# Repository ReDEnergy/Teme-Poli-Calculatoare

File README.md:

Golden Box
===============

#### Teme, proiecte si laboratoare - Calculatoare 2010 - 2014 - Politehnica Bucuresti  

	Autor: Gabriel Ivanica

Aici gasiti cam toate proiectele si temele pe care le-am avut de facut in cei 4 ani de facultate  
**Toate sunt implementari personale, exceptie facand cateva proiecte de echipa**

## ATENTIE
+ Scopul acestui repo nu e sa ofere o sursa de copy/paste am trecut materia... ci o sursa de informare, idei si ajutor
+ Temele vin insotite de explicatii extrem de detaliate in **README** (100+ linii) + bonus ASCII ART

**Daca se intampla sa aveti fix aceasi tema, nu fiti fraieri sa credeti ca va merge cu copy-paste**
+ asistentii se prind de la o posta cand e vorba de copiat si adio punctaj pe teme
+ deci, 99% sanse sa repeti materia daca copiezi

## Statistici
+ tot ce am pus compileaza si ruleaza 100%
+ 95% sunt complete 100/100 (in teste sau VM Checker) + bonus (daca exista)
+ in cazul in care lipsesc cerintele se pot deduce usor din README
+ facut aproape toate temele (exceptie, cateva cazuri limita de complexitate sau lene)
+ pentru anumite materii gasiti si laboratoare

## Recomandari
+ Cititi README, va uitati peste surse, rulati si testati, dar implementarea sa fie personala
+ Temele din anii III si IV sunt cele mai interesante si complexe
+ la SGP gasiti chestii interesante, foarte bune pentru proiectele de grafica din anii III sau IV (un mic Engine Grafic, tehnici de randare: deferred rendering, screen space ambient occlusion, shadows, tesselation, si multe altele)

##### Daca aveti sugestii sau recomandari adaugati un *issue*

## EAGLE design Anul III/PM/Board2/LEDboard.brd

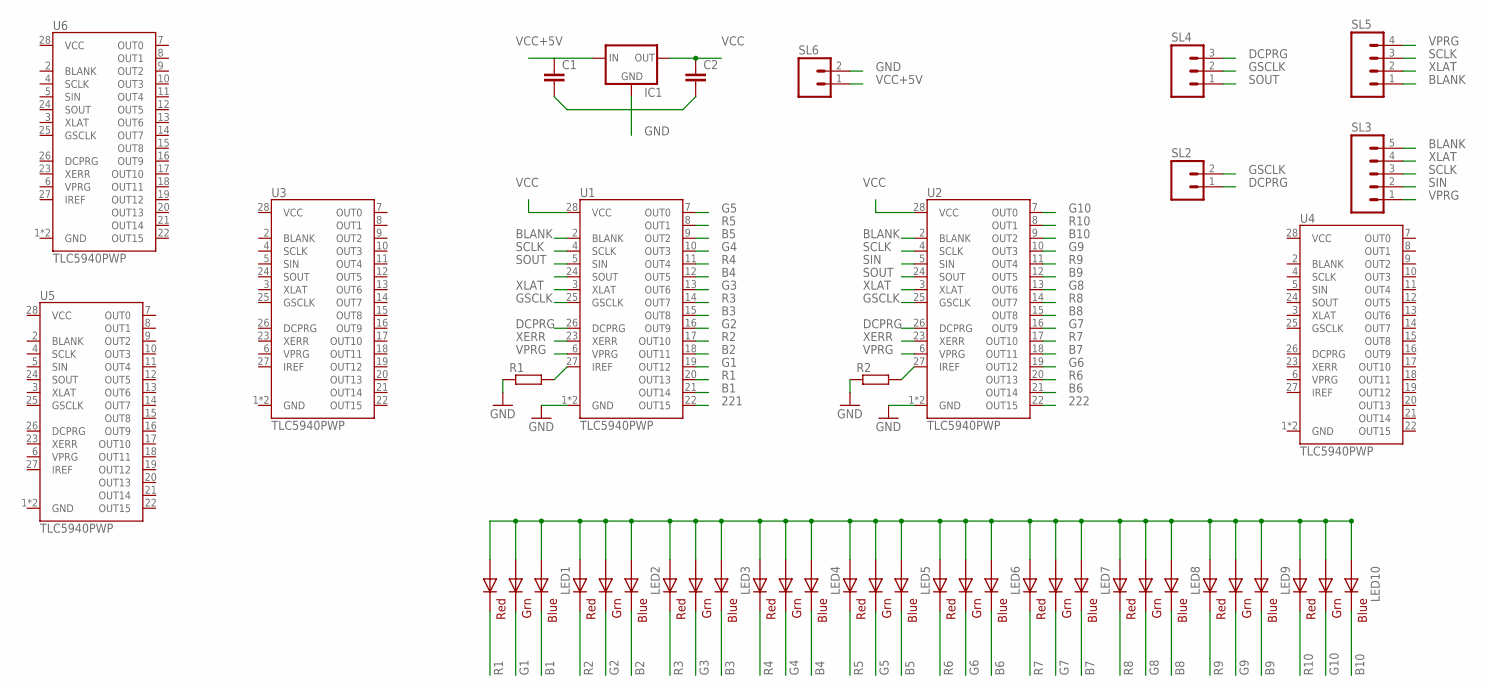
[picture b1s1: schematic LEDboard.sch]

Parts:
C1, C2: C-EU050-025X075; C050-025X075
IC1: 78XXL
LED1, LED2, LED3, LED4, LED5, LED6, LED7, LED8, LED9, LED10: RGBLED5050
R1, R2: R-EU_M1406; M1406
SL2, SL6: M02; 02P
SL3: M05; 05P
SL4: M03; 03P
SL5: M04; 04P
U1, U2, U3, U4, U5, U6: TLC5940PWP; TSSOP28-GROUNDPAD

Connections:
221: U1.22 (OUT15)
222: U2.22 (OUT15)
B1: LED1.4 (BLUE_C), U1.21 (OUT14)
B2: LED2.4 (BLUE_C), U1.18 (OUT11)
B3: LED3.4 (BLUE_C), U1.15 (OUT8)
B4: LED4.4 (BLUE_C), U1.12 (OUT5)
B5: LED5.4 (BLUE_C), U1.9 (OUT2)
B6: LED6.4 (BLUE_C), U2.21 (OUT14)
B7: LED7.4 (BLUE_C), U2.18 (OUT11)
B8: LED8.4 (BLUE_C), U2.15 (OUT8)
B9: LED9.4 (BLUE_C), U2.12 (OUT5)
B10: LED10.4 (BLUE_C), U2.9 (OUT2)
BLANK: SL3.5, SL5.1, U1.2 (BLANK), U2.2 (BLANK)
DCPRG: SL2.1, SL4.3, U1.26 (DCPRG), U2.26 (DCPRG)
G1: LED1.6 (GREEN_C), U1.19 (OUT12)
G2: LED2.6 (GREEN_C), U1.16 (OUT9)
G3: LED3.6 (GREEN_C), U1.13 (OUT6)
G4: LED4.6 (GREEN_C), U1.10 (OUT3)
G5: LED5.6 (GREEN_C), U1.7 (OUT0)
G6: LED6.6 (GREEN_C), U2.19 (OUT12)
G7: LED7.6 (GREEN_C), U2.16 (OUT9)
G8: LED8.6 (GREEN_C), U2.13 (OUT6)
G9: LED9.6 (GREEN_C), U2.10 (OUT3)
G10: LED10.6 (GREEN_C), U2.7 (OUT0)
GND: C1.2, C2.2, IC1.GND, R1.1, R2.1, SL6.2, U1.1 (GND), U1.29 (GND), U2.1 (GND), U2.29 (GND)
GSCLK: SL2.2, SL4.2, U1.25 (GSCLK), U2.25 (GSCLK)
IREF: R1.2, R2.2, U1.27 (IREF), U2.27 (IREF)
R1: LED1.5 (RED_C), U1.20 (OUT13)
R2: LED2.5 (RED_C), U1.17 (OUT10)
R3: LED3.5 (RED_C), U1.14 (OUT7)
R4: LED4.5 (RED_C), U1.11 (OUT4)
R5: LED5.5 (RED_C), U1.8 (OUT1)
R6: LED6.5 (RED_C), U2.20 (OUT13)
R7: LED7.5 (RED_C), U2.17 (OUT10)
R8: LED8.5 (RED_C), U2.14 (OUT7)
R9: LED9.5 (RED_C), U2.11 (OUT4)
R10: LED10.5 (RED_C), U2.8 (OUT1)
SCLK: SL3.3, SL5.3, U1.4 (SCLK), U2.4 (SCLK)
SIN: SL3.2, U2.5 (SIN)
SOUT: SL4.1, U1.5 (SIN), U1.24 (SOUT), U2.24 (SOUT)
VCC: C2.1, IC1.OUT, LED1.1 (GREEN_A), LED1.2 (RED_A), LED1.3 (BLUE_A), LED2.1 (GREEN_A), LED2.2 (RED_A), LED2.3 (BLUE_A), LED3.1 (GREEN_A), LED3.2 (RED_A), LED3.3 (BLUE_A), LED4.1 (GREEN_A), LED4.2 (RED_A), LED4.3 (BLUE_A), LED5.1 (GREEN_A), LED5.2 (RED_A), LED5.3 (BLUE_A), LED6.1 (GREEN_A), LED6.2 (RED_A), LED6.3 (BLUE_A), LED7.1 (GREEN_A), LED7.2 (RED_A), LED7.3 (BLUE_A), LED8.1 (GREEN_A), LED8.2 (RED_A), LED8.3 (BLUE_A), LED9.1 (GREEN_A), LED9.2 (RED_A), LED9.3 (BLUE_A), LED10.1 (GREEN_A), LED10.2 (RED_A), LED10.3 (BLUE_A), U1.28 (VCC), U2.28 (VCC)
VCC+5V: C1.1, IC1.IN, SL6.1
VPRG: SL3.1, SL5.4, U1.6 (VPRG), U2.6 (VPRG)
XERR: U1.23 (XERR), U2.23 (XERR)
XLAT: SL3.4, SL5.2, U1.3 (XLAT), U2.3 (XLAT)

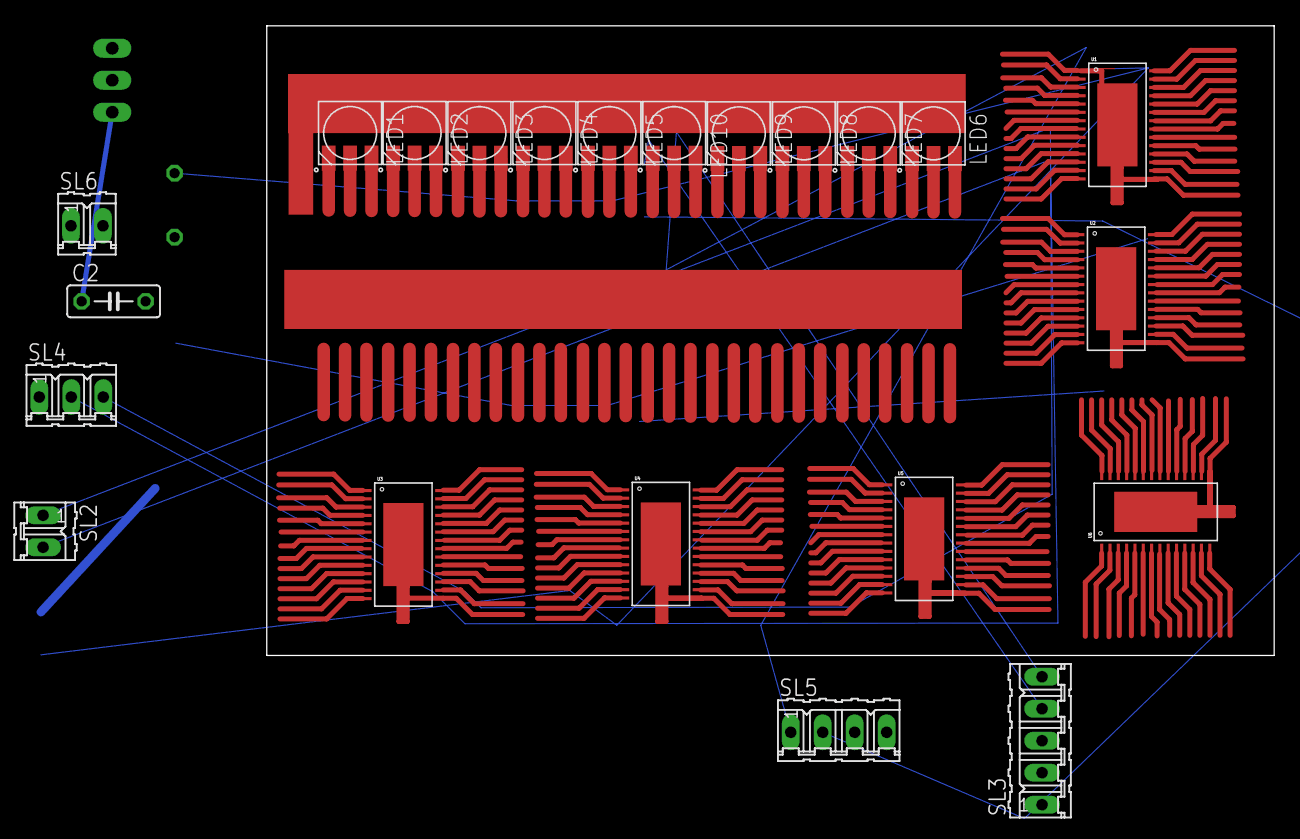
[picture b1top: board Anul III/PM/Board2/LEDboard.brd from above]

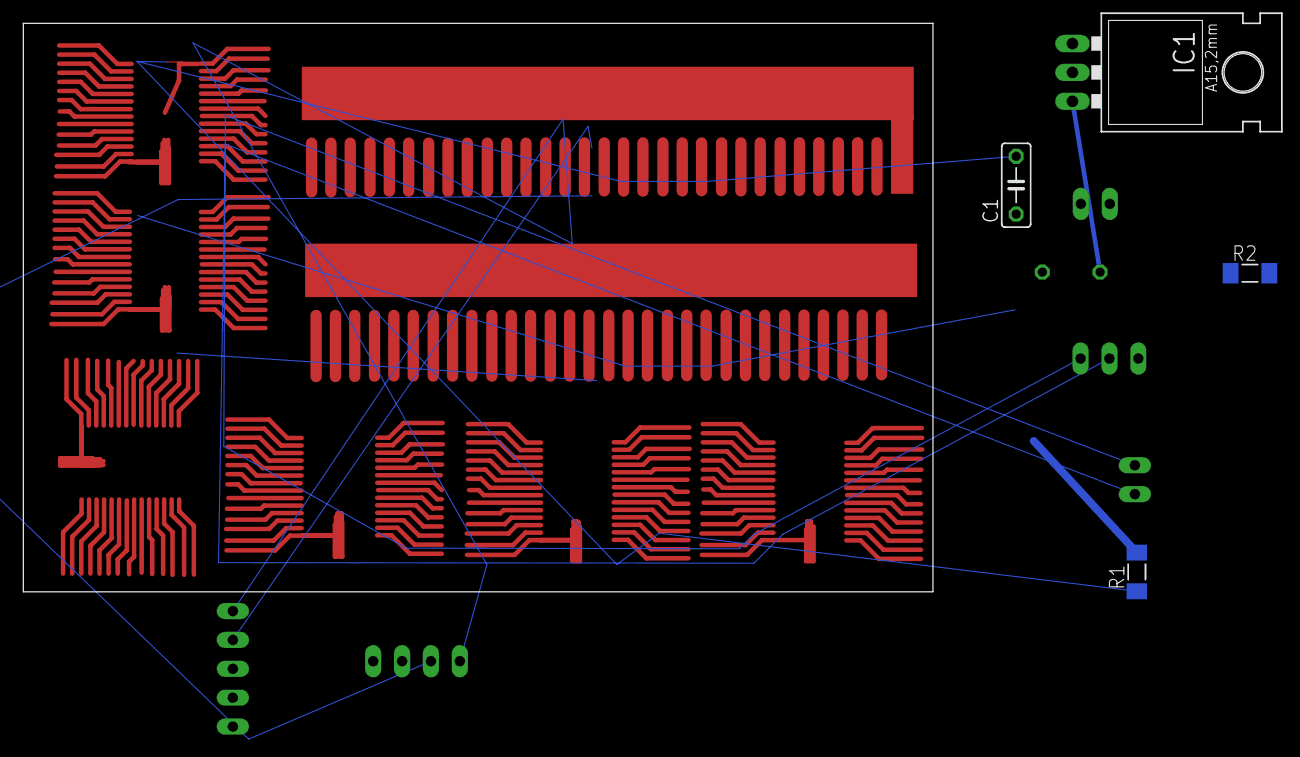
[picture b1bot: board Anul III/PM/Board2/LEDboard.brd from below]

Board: 2 copper layers, 26 parts (4 on the bottom side), 43 nets.

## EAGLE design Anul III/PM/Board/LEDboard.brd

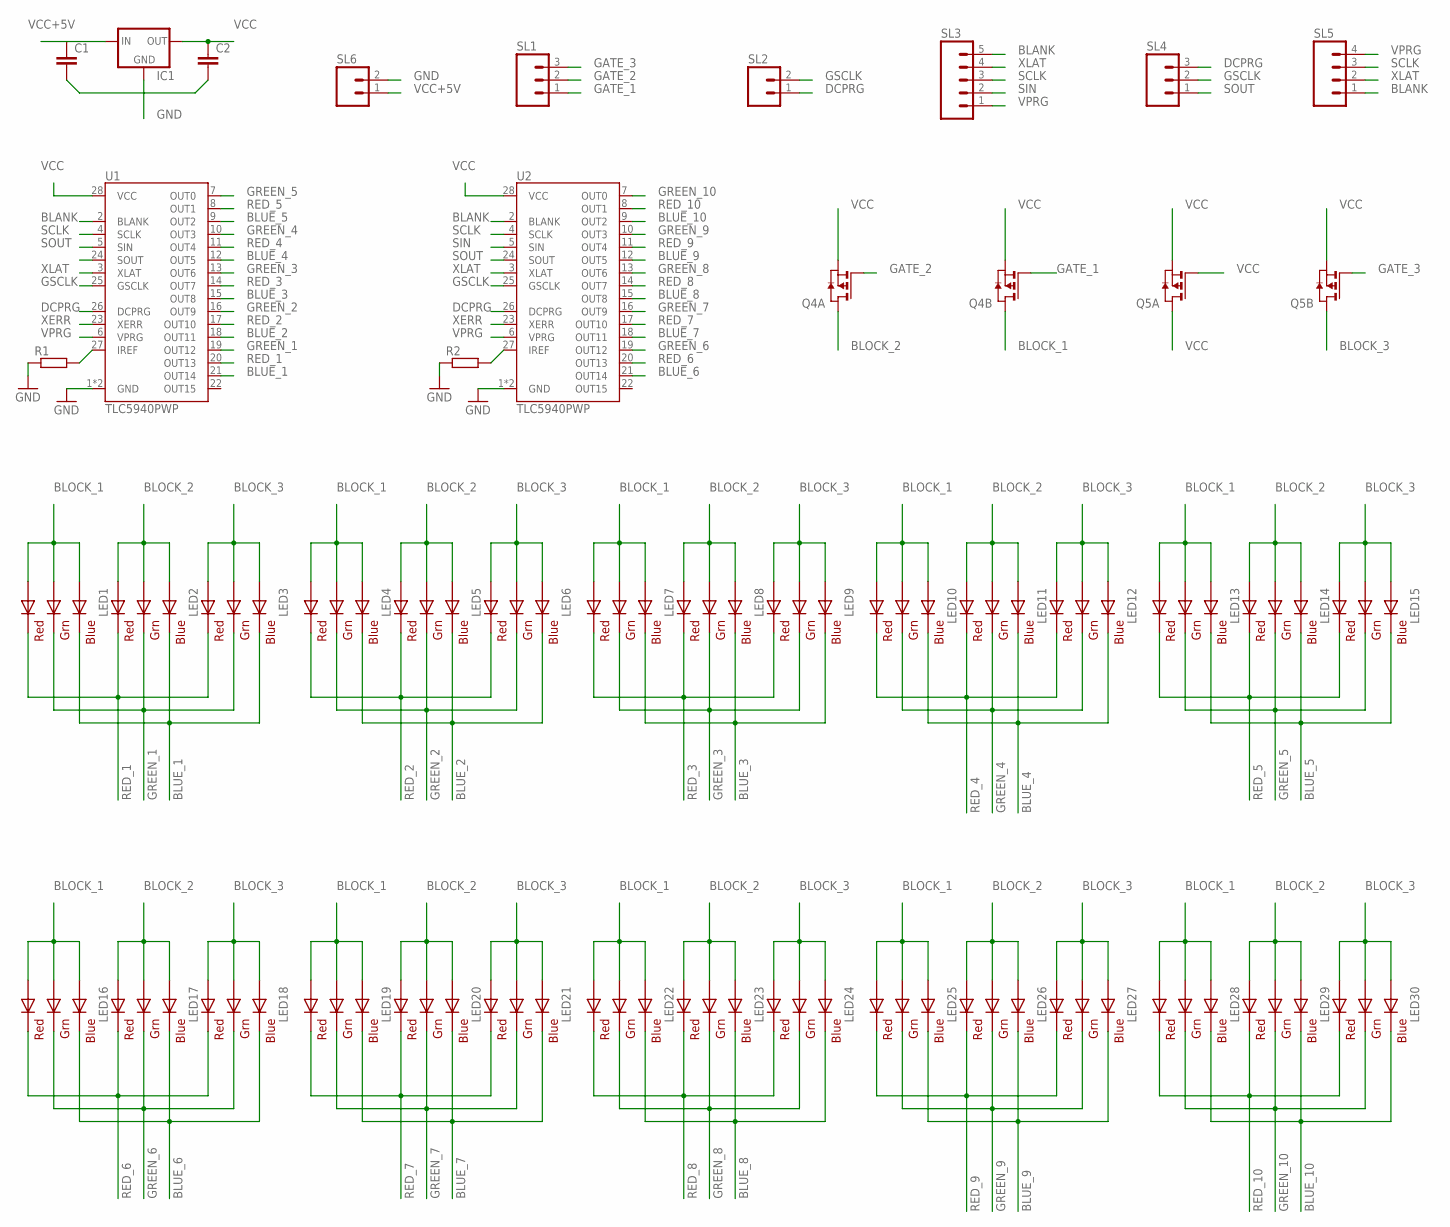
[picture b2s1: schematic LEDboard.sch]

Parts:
C1, C2: C-EU050-025X075; C050-025X075
IC1: 78XXL
LED1, LED2, LED3, LED4, LED5, LED6, LED7, LED8, LED9, LED10, LED11, LED12, LED13, LED14, LED15, LED16, LED17, LED18, LED19, LED20, LED21, LED22, LED23, LED24, LED25, LED26, LED27, LED28, LED29, LED30: RGBLED5050
Q4, Q5: PN_MOSFET-SO8; SO8
R1, R2: R-EU_M1406; M1406
SL1, SL4: M03; 03P
SL2, SL6: M02; 02P
SL3: M05; 05P
SL5: M04; 04P
U1, U2: TLC5940PWP; TSSOP28-GROUNDPAD

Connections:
BLANK: SL3.5, SL5.1, U1.2 (BLANK), U2.2 (BLANK)
BLOCK_1: LED1.1 (GREEN_A), LED1.2 (RED_A), LED1.3 (BLUE_A), LED4.1 (GREEN_A), LED4.2 (RED_A), LED4.3 (BLUE_A), LED7.1 (GREEN_A), LED7.2 (RED_A), LED7.3 (BLUE_A), LED10.1 (GREEN_A), LED10.2 (RED_A), LED10.3 (BLUE_A), LED13.1 (GREEN_A), LED13.2 (RED_A), LED13.3 (BLUE_A), LED16.1 (GREEN_A), LED16.2 (RED_A), LED16.3 (BLUE_A), LED19.1 (GREEN_A), LED19.2 (RED_A), LED19.3 (BLUE_A), LED22.1 (GREEN_A), LED22.2 (RED_A), LED22.3 (BLUE_A), LED25.1 (GREEN_A), LED25.2 (RED_A), LED25.3 (BLUE_A), LED28.1 (GREEN_A), LED28.2 (RED_A), LED28.3 (BLUE_A), Q4.5 (D), Q4.6 (D)
BLOCK_2: LED2.1 (GREEN_A), LED2.2 (RED_A), LED2.3 (BLUE_A), LED5.1 (GREEN_A), LED5.2 (RED_A), LED5.3 (BLUE_A), LED8.1 (GREEN_A), LED8.2 (RED_A), LED8.3 (BLUE_A), LED11.1 (GREEN_A), LED11.2 (RED_A), LED11.3 (BLUE_A), LED14.1 (GREEN_A), LED14.2 (RED_A), LED14.3 (BLUE_A), LED17.1 (GREEN_A), LED17.2 (RED_A), LED17.3 (BLUE_A), LED20.1 (GREEN_A), LED20.2 (RED_A), LED20.3 (BLUE_A), LED23.1 (GREEN_A), LED23.2 (RED_A), LED23.3 (BLUE_A), LED26.1 (GREEN_A), LED26.2 (RED_A), LED26.3 (BLUE_A), LED29.1 (GREEN_A), LED29.2 (RED_A), LED29.3 (BLUE_A), Q4.7 (D), Q4.8 (D)
BLOCK_3: LED3.1 (GREEN_A), LED3.2 (RED_A), LED3.3 (BLUE_A), LED6.1 (GREEN_A), LED6.2 (RED_A), LED6.3 (BLUE_A), LED9.1 (GREEN_A), LED9.2 (RED_A), LED9.3 (BLUE_A), LED12.1 (GREEN_A), LED12.2 (RED_A), LED12.3 (BLUE_A), LED15.1 (GREEN_A), LED15.2 (RED_A), LED15.3 (BLUE_A), LED18.1 (GREEN_A), LED18.2 (RED_A), LED18.3 (BLUE_A), LED21.1 (GREEN_A), LED21.2 (RED_A), LED21.3 (BLUE_A), LED24.1 (GREEN_A), LED24.2 (RED_A), LED24.3 (BLUE_A), LED27.1 (GREEN_A), LED27.2 (RED_A), LED27.3 (BLUE_A), LED30.1 (GREEN_A), LED30.2 (RED_A), LED30.3 (BLUE_A), Q5.5 (D), Q5.6 (D)
BLUE_1: LED1.4 (BLUE_C), LED2.4 (BLUE_C), LED3.4 (BLUE_C), U1.21 (OUT14)
BLUE_2: LED4.4 (BLUE_C), LED5.4 (BLUE_C), LED6.4 (BLUE_C), U1.18 (OUT11)
BLUE_3: LED7.4 (BLUE_C), LED8.4 (BLUE_C), LED9.4 (BLUE_C), U1.15 (OUT8)
BLUE_4: LED10.4 (BLUE_C), LED11.4 (BLUE_C), LED12.4 (BLUE_C), U1.12 (OUT5)
BLUE_5: LED13.4 (BLUE_C), LED14.4 (BLUE_C), LED15.4 (BLUE_C), U1.9 (OUT2)
BLUE_6: LED16.4 (BLUE_C), LED17.4 (BLUE_C), LED18.4 (BLUE_C), U2.21 (OUT14)
BLUE_7: LED19.4 (BLUE_C), LED20.4 (BLUE_C), LED21.4 (BLUE_C), U2.18 (OUT11)
BLUE_8: LED22.4 (BLUE_C), LED23.4 (BLUE_C), LED24.4 (BLUE_C), U2.15 (OUT8)
BLUE_9: LED25.4 (BLUE_C), LED26.4 (BLUE_C), LED27.4 (BLUE_C), U2.12 (OUT5)
BLUE_10: LED28.4 (BLUE_C), LED29.4 (BLUE_C), LED30.4 (BLUE_C), U2.9 (OUT2)
DCPRG: SL2.1, SL4.3, U1.26 (DCPRG), U2.26 (DCPRG)
GATE_1: Q4.4 (G), SL1.1
GATE_2: Q4.2 (G), SL1.2
GATE_3: Q5.4 (G), SL1.3
GND: C1.2, C2.2, IC1.GND, R1.1, R2.1, SL6.2, U1.1 (GND), U1.29 (GND), U2.1 (GND), U2.29 (GND)
GREEN_1: LED1.6 (GREEN_C), LED2.6 (GREEN_C), LED3.6 (GREEN_C), U1.19 (OUT12)
GREEN_2: LED4.6 (GREEN_C), LED5.6 (GREEN_C), LED6.6 (GREEN_C), U1.16 (OUT9)
GREEN_3: LED7.6 (GREEN_C), LED8.6 (GREEN_C), LED9.6 (GREEN_C), U1.13 (OUT6)
GREEN_4: LED10.6 (GREEN_C), LED11.6 (GREEN_C), LED12.6 (GREEN_C), U1.10 (OUT3)
GREEN_5: LED13.6 (GREEN_C), LED14.6 (GREEN_C), LED15.6 (GREEN_C), U1.7 (OUT0)
GREEN_6: LED16.6 (GREEN_C), LED17.6 (GREEN_C), LED18.6 (GREEN_C), U2.19 (OUT12)
GREEN_7: LED19.6 (GREEN_C), LED20.6 (GREEN_C), LED21.6 (GREEN_C), U2.16 (OUT9)
GREEN_8: LED22.6 (GREEN_C), LED23.6 (GREEN_C), LED24.6 (GREEN_C), U2.13 (OUT6)
GREEN_9: LED25.6 (GREEN_C), LED26.6 (GREEN_C), LED27.6 (GREEN_C), U2.10 (OUT3)
GREEN_10: LED28.6 (GREEN_C), LED29.6 (GREEN_C), LED30.6 (GREEN_C), U2.7 (OUT0)
GSCLK: SL2.2, SL4.2, U1.25 (GSCLK), U2.25 (GSCLK)
unnamed: R2.2, U2.27 (IREF)
unnamed: R1.2, U1.27 (IREF)
RED_1: LED1.5 (RED_C), LED2.5 (RED_C), LED3.5 (RED_C), U1.20 (OUT13)
RED_2: LED4.5 (RED_C), LED5.5 (RED_C), LED6.5 (RED_C), U1.17 (OUT10)
RED_3: LED7.5 (RED_C), LED8.5 (RED_C), LED9.5 (RED_C), U1.14 (OUT7)
RED_4: LED10.5 (RED_C), LED11.5 (RED_C), LED12.5 (RED_C), U1.11 (OUT4)
RED_5: LED13.5 (RED_C), LED14.5 (RED_C), LED15.5 (RED_C), U1.8 (OUT1)
RED_6: LED16.5 (RED_C), LED17.5 (RED_C), LED18.5 (RED_C), U2.20 (OUT13)
RED_7: LED19.5 (RED_C), LED20.5 (RED_C), LED21.5 (RED_C), U2.17 (OUT10)
RED_8: LED22.5 (RED_C), LED23.5 (RED_C), LED24.5 (RED_C), U2.14 (OUT7)
RED_9: LED25.5 (RED_C), LED26.5 (RED_C), LED27.5 (RED_C), U2.11 (OUT4)
RED_10: LED28.5 (RED_C), LED29.5 (RED_C), LED30.5 (RED_C), U2.8 (OUT1)
SCLK: SL3.3, SL5.3, U1.4 (SCLK), U2.4 (SCLK)
SIN: SL3.2, U2.5 (SIN)
SOUT: SL4.1, U1.5 (SIN), U1.24 (SOUT), U2.24 (SOUT)
VCC: C2.1, IC1.OUT, Q4.1 (S), Q4.3 (S), Q5.1 (S), Q5.2 (G), Q5.3 (S), Q5.7 (D), Q5.8 (D), U1.28 (VCC), U2.28 (VCC)
VCC+5V: C1.1, IC1.IN, SL6.1
VPRG: SL3.1, SL5.4, U1.6 (VPRG), U2.6 (VPRG)
XERR: U1.23 (XERR), U2.23 (XERR)
XLAT: SL3.4, SL5.2, U1.3 (XLAT), U2.3 (XLAT)

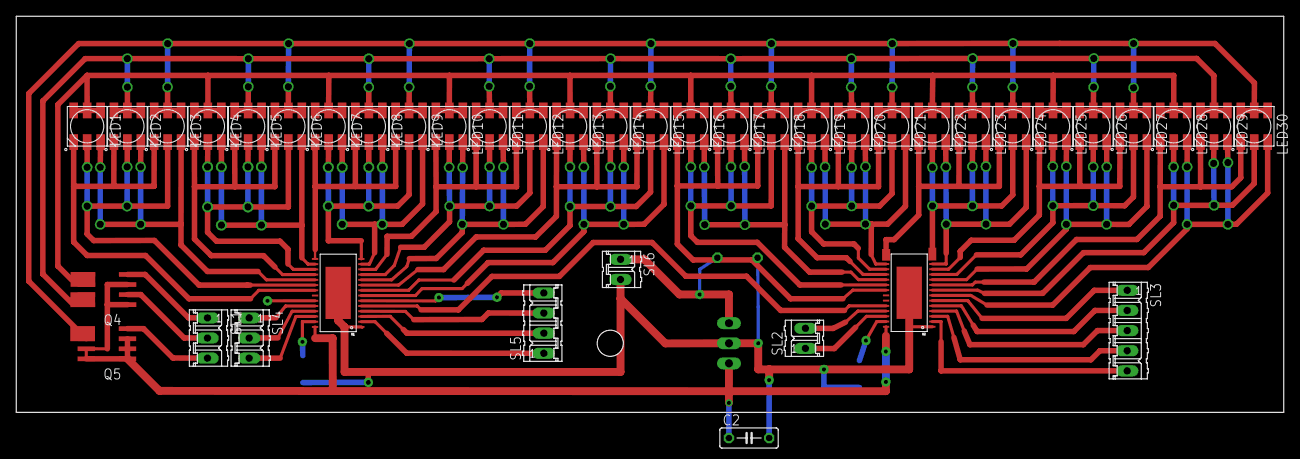
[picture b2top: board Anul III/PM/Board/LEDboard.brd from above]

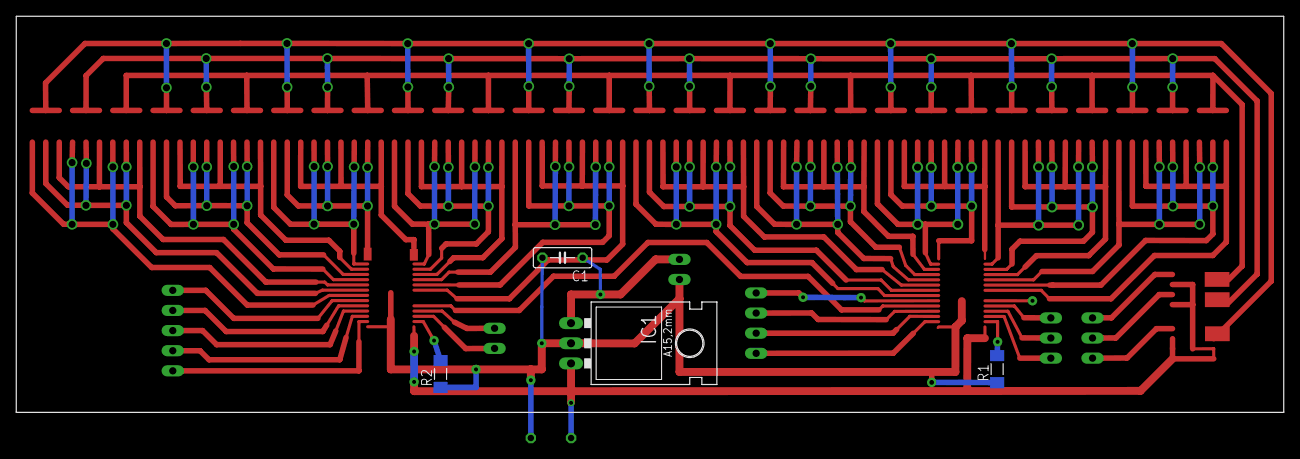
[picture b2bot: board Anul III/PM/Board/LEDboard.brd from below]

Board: 2 copper layers, 160.0 x 50.0 mm, 45 parts (4 on the bottom side), 50 nets.

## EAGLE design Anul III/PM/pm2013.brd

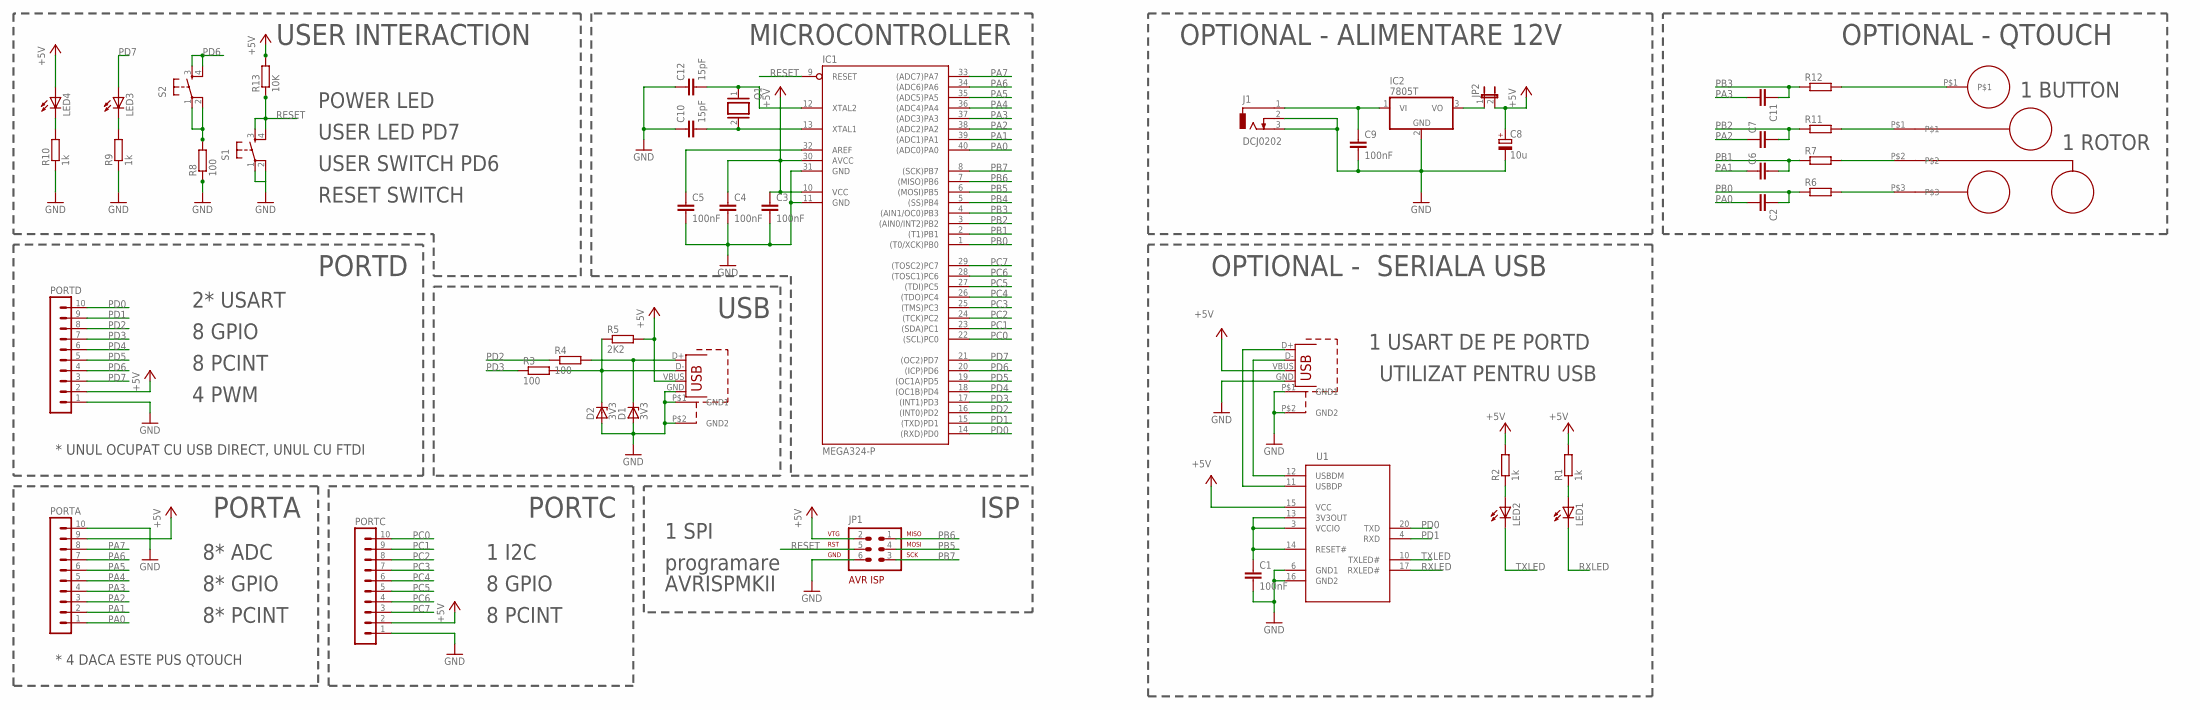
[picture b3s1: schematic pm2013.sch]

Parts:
C1, C3, C4, C5, C9: 100nF; C025-025X050
C2, C6, C7, C11: C-EUC1206; C1206
C8: 10u; E2,5-5
C10, C12: 15pF; C025-025X050
D1, D2: 3V3; DO34Z7
IC1: MEGA324-P; DIL40
IC2: 7805T; TO220H
J1: DCJ0202
JP1: AVR-ISP-6
JP2: JP1E; JP1
LED1, LED2, LED3, LED4: TLLR4400; LED3MM
PORTA: MA10-1W
PORTC: MA10-1W
PORTD: MA10-1W
Q1: XTAL/S; QS
R1, R2, R9, R10: 1k; 0204/7
R3, R4, R8: 100; 0204/7
R5: 2K2; 0204/7
R6, R7, R11, R12: R-EU_M1206; M1206
R13: 10K; 0204/7
S1, S2: TAC_SWITCHPTH; TACTILE-PTH
U1: FT231XS; SSOP20
U$1: ROTOR_ELECTRODE_TOUCH
U$2: SIMPLE_ELECTRODE_TOUCH
X1: USB; USB-B-PTH
X2: USBPTH; USB-B-PTH

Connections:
+5V: C3.1, C4.1, C8.+, IC1.10 (VCC), IC1.30 (AVCC), JP1.2, JP2.2, LED4.A, PORTA.9, PORTC.2, PORTD.2, R1.2, R2.2, R5.2, R13.2, U1.15 (VCC), X1.VBUS, X2.VBUS
GND: C1.2, C3.2, C4.2, C5.2, C8.-, C9.2, C10.1, C12.1, D1.A, D2.A, IC1.11 (GND), IC1.31 (GND), IC2.2 (GND), J1.2, J1.3, JP1.6, PORTA.10, PORTC.1, PORTD.1, R8.1, R9.1, R10.1, S1.1, S1.2, U1.6 (GND1), U1.16 (GND2), X1.GND, X1.P$1 (GND1), X1.P$2 (GND2), X2.GND, X2.P$1 (GND1), X2.P$2 (GND2)
unnamed: LED2.A, R2.1
unnamed: LED1.A, R1.1
unnamed: R11.2, U$1.P$1
unnamed: R7.2, U$1.P$2
unnamed: C1.1, U1.3 (VCCIO), U1.13 (3V3OUT), U1.14 (RESET#)
unnamed: R6.2, U$1.P$3
unnamed: D1.C, R4.2, X2.D+
unnamed: D2.C, R3.2, R5.1, X2.D-
unnamed: C9.1, IC2.1 (VI), J1.1
unnamed: R8.2, S2.1, S2.2
unnamed: IC2.3 (VO), JP2.1
unnamed: R12.2, U$2.P$1
unnamed: C5.1, IC1.32 (AREF)
unnamed: C10.2, IC1.13 (XTAL1), Q1.2
unnamed: C12.2, IC1.12 (XTAL2), Q1.1
unnamed: LED3.K (C), R9.2
unnamed: LED4.K (C), R10.2
PA0: C2.2, IC1.40 ((ADC0)PA0), PORTA.1
PA1: C6.1, IC1.39 ((ADC1)PA1), PORTA.2
PA2: C7.1, IC1.38 ((ADC2)PA2), PORTA.3
PA3: C11.2, IC1.37 ((ADC3)PA3), PORTA.4
PA4: IC1.36 ((ADC4)PA4), PORTA.5
PA5: IC1.35 ((ADC5)PA5), PORTA.6
PA6: IC1.34 ((ADC6)PA6), PORTA.7
PA7: IC1.33 ((ADC7)PA7), PORTA.8
PB0: C2.1, IC1.1 ((T0/XCK)PB0), R6.1
PB1: C6.2, IC1.2 ((T1)PB1), R7.1
PB2: C7.2, IC1.3 ((AIN0/INT2)PB2), R11.1
PB3: C11.1, IC1.4 ((AIN1/OC0)PB3), R12.1
PB4: IC1.5 ((SS)PB4)
PB5: IC1.6 ((MOSI)PB5), JP1.4
PB6: IC1.7 ((MISO)PB6), JP1.1
PB7: IC1.8 ((SCK)PB7), JP1.3
PC0: IC1.22 ((SCL)PC0), PORTC.10
PC1: IC1.23 ((SDA)PC1), PORTC.9
PC2: IC1.24 ((TCK)PC2), PORTC.8
PC3: IC1.25 ((TMS)PC3), PORTC.7
PC4: IC1.26 ((TDO)PC4), PORTC.6
PC5: IC1.27 ((TDI)PC5), PORTC.5
PC6: IC1.28 ((TOSC1)PC6), PORTC.4
PC7: IC1.29 ((TOSC2)PC7), PORTC.3
PD0: IC1.14 ((RXD)PD0), PORTD.10, U1.20 (TXD)
PD1: IC1.15 ((TXD)PD1), PORTD.9, U1.4 (RXD)
PD2: IC1.16 ((INT0)PD2), PORTD.8, R4.1
PD3: IC1.17 ((INT1)PD3), PORTD.7, R3.1
PD4: IC1.18 ((OC1B)PD4), PORTD.6
PD5: IC1.19 ((OC1A)PD5), PORTD.5
PD6: IC1.20 ((ICP)PD6), PORTD.4, S2.3, S2.4
PD7: IC1.21 ((OC2)PD7), LED3.A, PORTD.3
RESET: IC1.9 (RESET), JP1.5, R13.1, S1.3, S1.4
RXLED: LED1.K (C), U1.17 (RXLED#)
TXLED: LED2.K (C), U1.10 (TXLED#)
USB_D+: U1.11 (USBDP), X1.D+
USB_D-: U1.12 (USBDM), X1.D-

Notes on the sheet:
8* ADC
8* GPIO
8* PCINT
* 4 DACA ESTE PUS QTOUCH
1 I2C
8 GPIO
8 PCINT
2* USART
* UNUL OCUPAT CU USB DIRECT, UNUL CU FTDI
4 PWM
1 SPI
programare
AVRISPMKII
PORTA
PORTC
PORTD
USB
ISP
POWER LED
USER LED PD7
USER SWITCH PD6
RESET SWITCH
USER INTERACTION
MICROCONTROLLER
OPTIONAL - ALIMENTARE 12V
OPTIONAL - QTOUCH
OPTIONAL - SERIALA USB
1 BUTTON
1 ROTOR
1 USART DE PE PORTD
UTILIZAT PENTRU USB

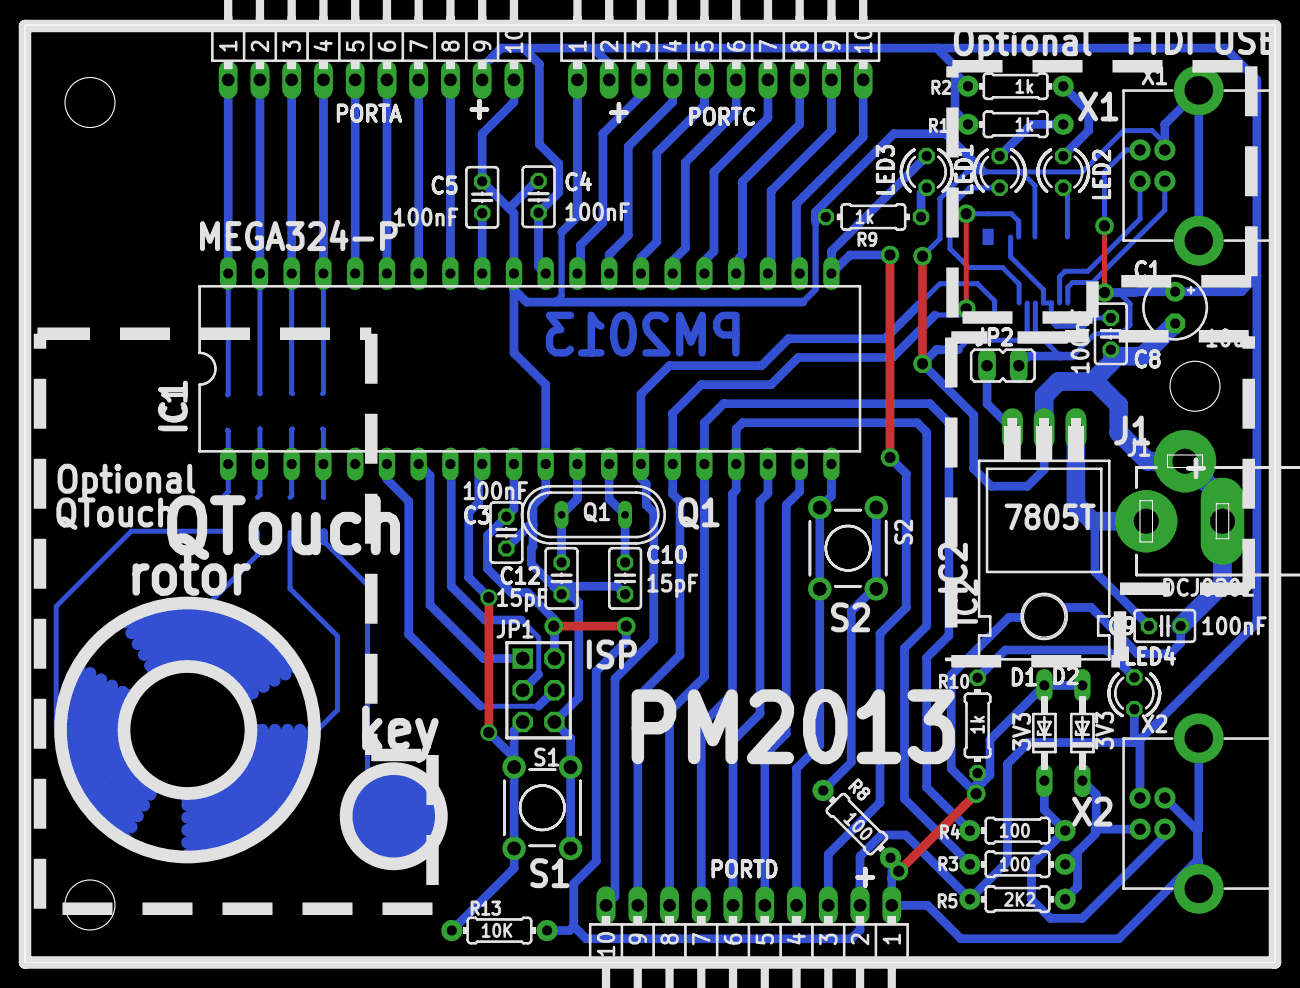
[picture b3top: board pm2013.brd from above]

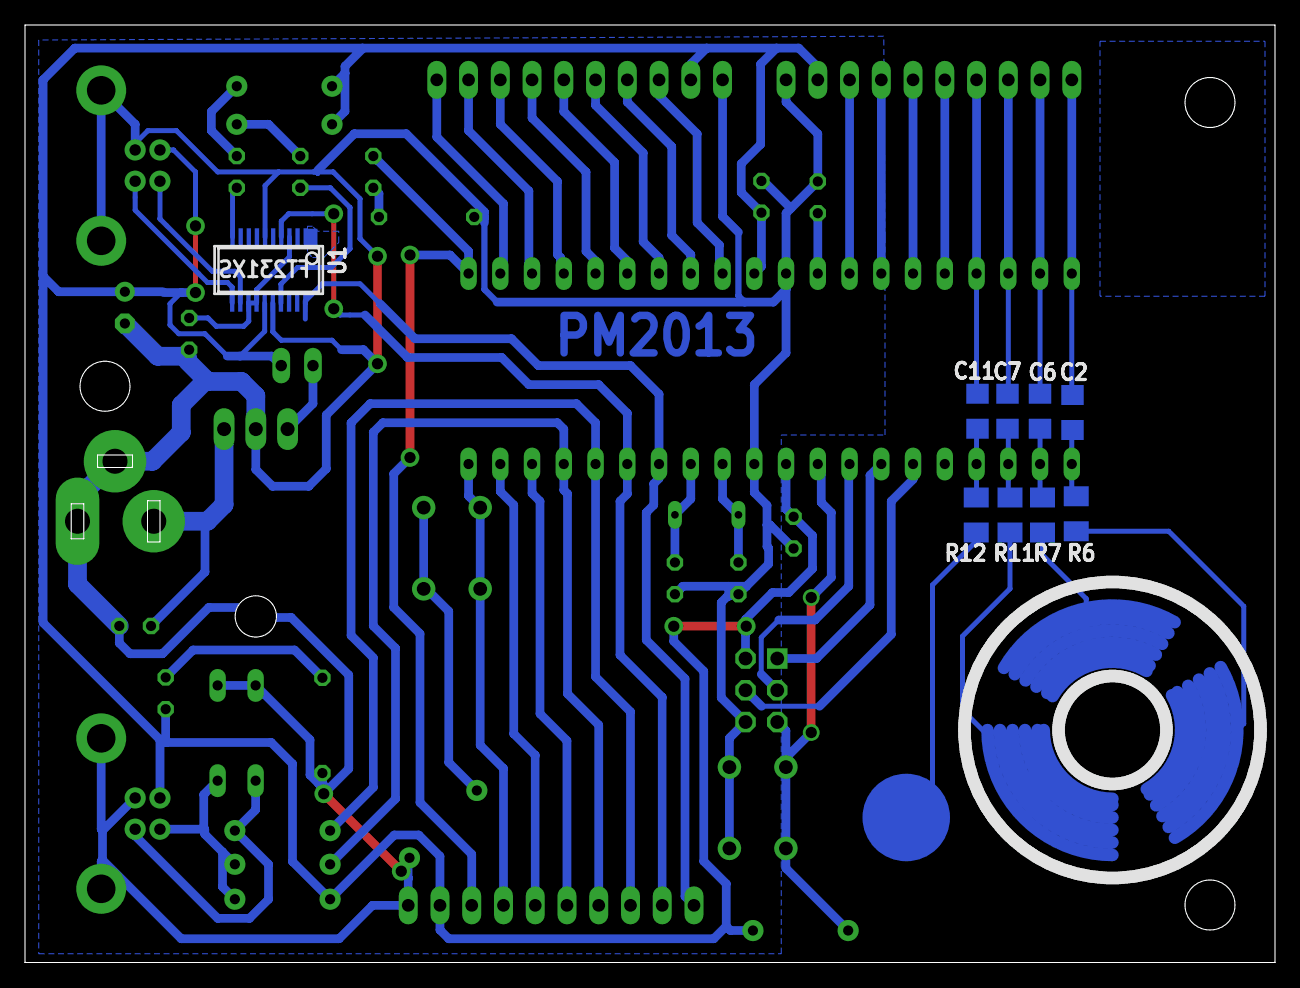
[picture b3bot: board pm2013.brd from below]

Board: 2 copper layers, 100.0 x 75.0 mm, 47 parts (11 on the bottom side), 55 nets.

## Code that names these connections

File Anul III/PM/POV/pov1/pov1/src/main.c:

/**
 * \file
 *
 * \brief Empty user application template
 *
 */

/**
 * \mainpage User Application template doxygen documentation
 *
 * \par Empty user application template
 *
 * Bare minimum empty user application template
 *
 * \par Content
 *
 * -# Include the ASF header files (through asf.h)
 * -# Minimal main function that starts with a call to board_init()
 * -# "Insert application code here" comment
 *
 */

/*
 * Include header files for all drivers that have been imported from
 * Atmel Software Framework (ASF).
 */
#include <asf.h>
#include <avr/io.h>
#include <avr/interrupt.h>
#define F_CPU 16000000
#include <util/delay.h>

char led[2][16] = {
	{0, 1, 2, 3, 4, 5, 0, 1, 2, 3, 4, 5, 6, 7, 1, 2},
	{3, 3, 3, 3, 3, 3, 2, 2, 2, 2, 2, 2, 2, 2, 0, 0}
};

unsigned char volatile* ports[] = {&PORTA, &PORTB, &PORTC, &PORTD};
unsigned char pins[] = {0, 1, 2, 3, 4};

char F[16][24] = {
	"111111111111111111111111",
	"111111111111111111111111",
	"111111111111111111111111",
	"111111111111111111111111",
	"111111100000000000000000",
	"111111100000000000000000",
	"111111100000000000000000",
	"111111111111111111000000",
	"111111111111111111000000",
	"111111111111111111000000",
	"111111100000000000000000",
	"111111100000000000000000",
	"111111100000000000000000",
	"111111100000000000000000",
	"111111100000000000000000",
	"111111100000000000000000",
	};


int step = 0;

ISR(TIMER1_COMPA_vect)
{

	PORTC ^= ((1 << 6) - 1);	// LED 
	PORTD ^= ((1 << 6) - 1);
/*
	for (int i=0; i<16; i++) {
		if (F[i][step] == 0) {
			switch(led[1][i]) {
				case 3 :
					PORTD &= ~(1 << led[0][i]);
					break;
				case 0 :
					PORTA &= ~(1 << led[0][i]);
					break;
				case 2 :
					PORTC &= ~(1 << led[0][i]);
					break;
			}
		}

		else {
			switch(led[1][i]) {
				case 3 :
				PORTD |= 1 << led[0][i];
				break;
				case 0 :
				PORTA |= 1 << led[0][i];
				break;
				case 2 :
				PORTC |= 1 << led[0][i];
				break;
			}
		}
	}

	step++;
	if (step == 25)
		step = 0;
*/
}

int main (void)
{
	sei();
	board_init();

	// BUTON PD6
	DDRD &= ~(1 << PD6);  // BUTON - input
	PORTD |= (1 << PD6);  // activam rezistenta de pull-up
  
	// LED ROSU PD7
	DDRD |= (1 << PD7);   

	// LEDURI PORTD
	DDRD |= (1 << 6) - 1;		// PIN LEDURI output
	PORTD &= ~((1 << 6) - 1);	// LED OFF
	
	// LEDURI PORTC
	DDRC |= (1 << 8) - 1;		// PIN LEDURI output
	PORTC &= ~((1 << 8) - 1);	// LED OFF

	// LEDURI PORTA
	DDRA |= (1 << PA7);			
	DDRA |= (1 << PA6);
	PORTA &= ~(1 << PA6);
	PORTA &= ~(1 << PA7);
  
	// Timer
	TCCR1B |= (1 << WGM12);		// modul CTC - capitolul 16 din datasheet,
//	TCCR1A |= (1 << COM1B0);	// toggle pe OC1B la fiecare compare match
	TCCR1B |= (1 << CS12);		// prescaler 256 - capitolul 16
	TIMSK1 |= (1 << OCIE1A);
	OCR1A = 5000;				// 16000000 / 2 / 256 = 31250



	while (1)
	{
		if (!(PIND & (1 << PD6))) {
			// daca bitul corespunzator PD6 este 0
			// PORTD |= (1 << PD7);		// LED OFF
			PORTD &= ~((1 << 6) - 1);	// LED OFF
			PORTC &= ~((1 << 8) - 1);	// LED OFF
			PORTA &= ~(1 << PA6);		// LED OFF
			PORTA &= ~(1 << PA7);		// LED OFF
		}
		else {
			// PORTD &= ~(1 << PD7);		// LED ON
			PORTD |= ((1 << 6) - 1);	// LED ON
			PORTC |= (1 << 8) - 1;		// LED ON
			PORTA |= (1 << PA6);		// LED ON
			PORTA |= (1 << PA7);		// LED ON
		}


	}
	return 0;

	// Insert application code here, after the board has been initialized.
}

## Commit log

2017-05-21 Calculatoare

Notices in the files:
parts and their libraries:
SparkFun-DigitalIC: Licensing: CC v3.0 Share-Alike You are welcome to use this library for commercial purposes.
